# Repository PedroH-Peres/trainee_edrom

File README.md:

# EDROM - Trainee

<h1>Repositório para os exercícios Trainee</h1>

<h3>Capacitação:</h3>
<p>
  <li>Python</li>
  <li>ROS 2</li>
  <li>Ubuntu 22.04</li>
</p>
<h3>🧑‍💻 Pedro Henrique Bohling Peres -
Engenharia Mecatrônica </h3>

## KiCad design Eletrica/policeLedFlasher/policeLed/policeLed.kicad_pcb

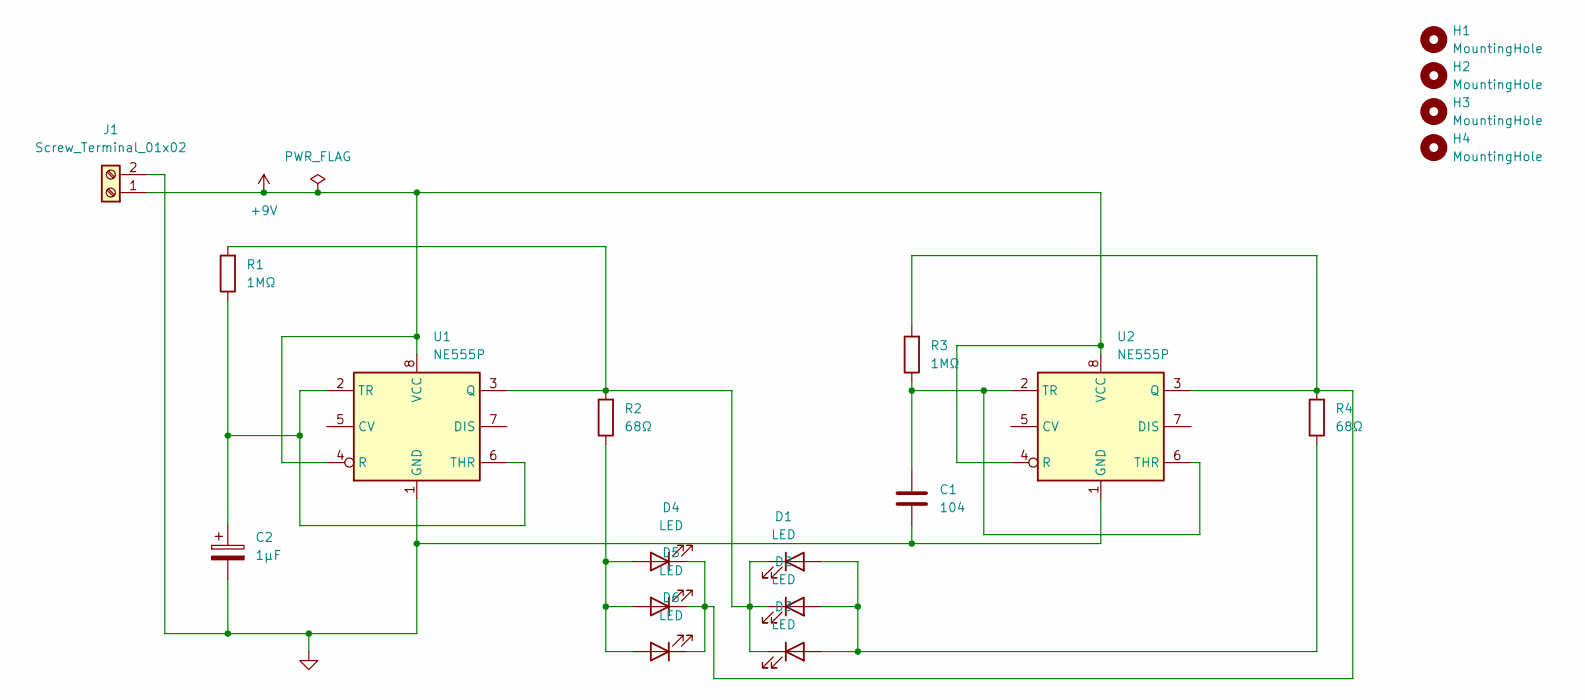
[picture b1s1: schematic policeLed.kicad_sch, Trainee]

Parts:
C1: 104; C_Disc_D3.4mm_W2.1mm_P2.50mm
C2: 1µF; CP_Radial_D4.0mm_P2.00mm
D1, D2, D3, D4, D5, D6: LED; LED_D5.0mm
H1, H2, H3, H4: MountingHole; MountingHole_2.5mm_Pad
J1: Screw_Terminal_01x02; TerminalBlock_bornier-2_P5.08mm
R1, R3: 1MΩ; R_Axial_DIN0204_L3.6mm_D1.6mm_P7.62mm_Horizontal
R2, R4: 68Ω; R_Axial_DIN0204_L3.6mm_D1.6mm_P7.62mm_Horizontal
U1, U2: NE555P; DIP-8_W7.62mm

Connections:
+9V: J1.1, U1.4 (R), U1.8 (VCC), U2.4 (R), U2.8 (VCC)
GND: C1.2, C2.2, J1.2, U1.1 (GND), U2.1 (GND)
unnamed: D1.2 (A), D2.2 (A), D3.2 (A), R4.1
unnamed: D1.1 (K), D2.1 (K), D3.1 (K), R1.2, R2.2, U1.3 (Q)
unnamed: D4.2 (A), D5.2 (A), D6.2 (A), R2.1
unnamed: D4.1 (K), D5.1 (K), D6.1 (K), R3.2, R4.2, U2.3 (Q)
unnamed: C2.1, R1.1, U1.2 (TR), U1.6 (THR)
unnamed: C1.1, R3.1, U2.2 (TR), U2.6 (THR)

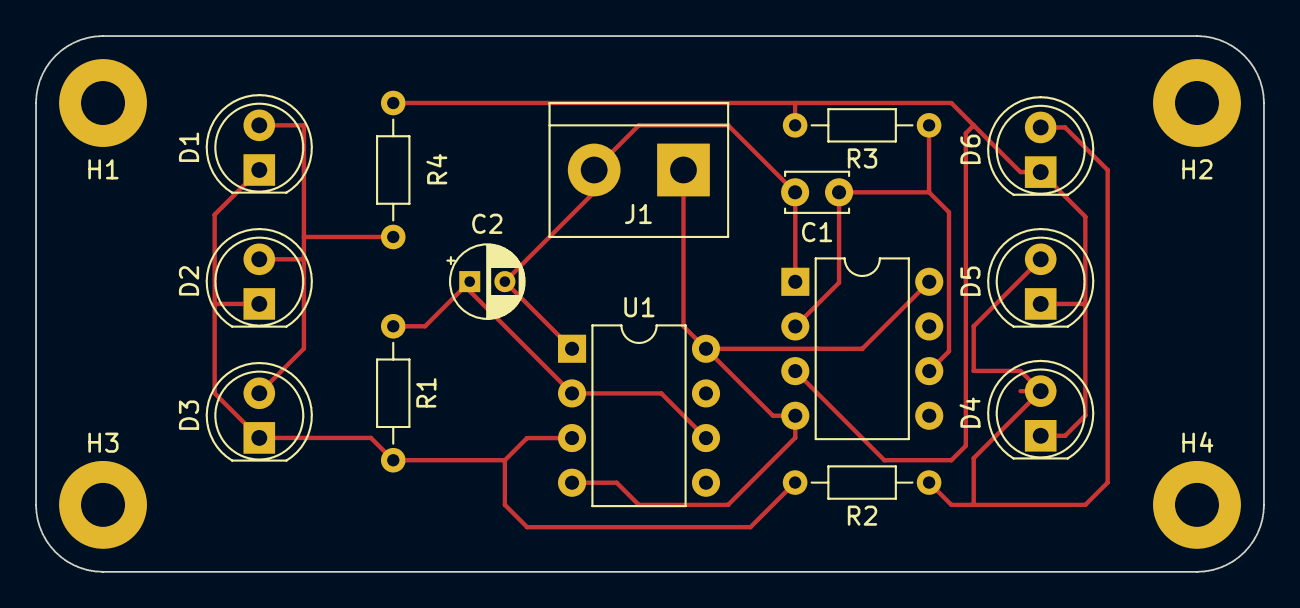
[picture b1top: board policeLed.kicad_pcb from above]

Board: 2 copper layers, 69.9 x 30.5 mm, 19 parts (0 on the bottom side), 8 nets.

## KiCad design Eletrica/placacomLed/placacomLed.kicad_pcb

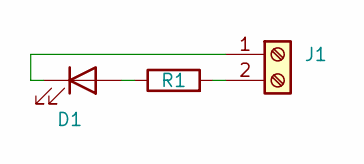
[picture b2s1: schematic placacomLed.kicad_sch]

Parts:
D1: LED; LED_D3.0mm
J1: Screw_Terminal_01x02; TerminalBlock_4Ucon_1x02_P3.50mm_Horizontal
R1: R; R_Axial_DIN0411_L9.9mm_D3.6mm_P12.70mm_Horizontal

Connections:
unnamed: D1.2 (A), R1.1
unnamed: D1.1 (K), J1.1
unnamed: J1.2, R1.2

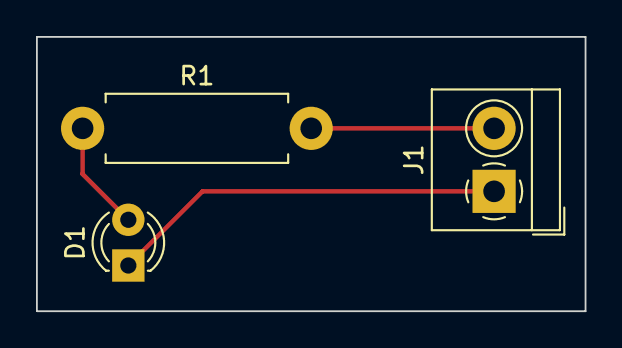
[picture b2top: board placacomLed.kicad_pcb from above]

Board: 2 copper layers, 30.5 x 15.2 mm, 3 parts (0 on the bottom side), 3 nets.

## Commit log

2023-11-24 initial
2023-11-24 trab1
2023-11-24 trab1-repos
2023-11-26 pyexercises
2023-11-26 Exercises
2023-11-26 more exercises
2023-11-27 2 exercises
2023-11-27 More 1 Medium
2023-11-27 more
2023-11-27 rename
2023-11-27 Easy exercises
2023-11-30 More easy exercises
2023-11-30 Ros2 Init
2023-11-30 Py easy
2023-12-01 '033'
2023-12-01 ROSNodes
2023-12-01 Set e regex
2023-12-02 37-40(easy)
2023-12-03 More ROS2
2023-12-04 41-45
2023-12-04 46-50
2023-12-06 51 e 52
2023-12-06 More Exerc
2023-12-06 More 2
2023-12-07 Estrutura 1
2023-12-07 Create linkutil
2023-12-08 More More
2023-12-08 ROS2 Understanding Services
2023-12-10 HTML exercises
2023-12-10 Parameters ROS 2
2023-12-11 More Py
2023-12-12 72-75
2023-12-14 Behaviour Task 1
2023-12-15 Python Py Py
2023-12-16 78-80
2023-12-18 81-85
2023-12-20 Final Easy Py
2023-12-24 02 Medium
2024-01-07 More Medium
2024-01-08 Final Python Exercises
2024-01-12 eletrica
2024-01-13 Estrutura2
2024-01-13 Labels
2024-01-14 Eletrica2
2024-01-14 Visao1
2024-01-19 Behaviour 2
2024-01-23 ROS2 Back
2024-01-26 Ros2 Rqt & Nodes
2024-01-30 visao 2 e 3
2024-01-30 Ros2 Begginer finish
2024-01-31 Ros2
2024-02-02 Final
